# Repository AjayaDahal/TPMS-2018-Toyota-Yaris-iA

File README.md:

# TPMS monitor panel + blind-spot cameras (2018 Toyota Yaris iA)

A dash unit for the Yaris iA in two stages:

- **v1, TPMS panel (done; orderable after one fix):** receives the car's 315 MHz tyre-pressure (TPMS) sensors and shows the pressures on an OLED display, with four tyre LEDs and a rotary encoder. It is based on my ECE 6723 Embedded Systems project ([report](00-project-management/TPMS_project_report_ECE6723.pdf)).
- **v2, TPMS + blind-spot assist (designed; the carrier PCB is ready to order):** adds two mirror cameras with car/motorcycle detection on a Raspberry Pi 4, shown on your SunFounder TS-7 7" HDMI touch display (1024 × 600 IPS). When a vehicle is in a blind spot, an amber LED lights in that door sail; signalling towards it sounds a sharp beep and shows that camera. The touch screen replaces the v1 encoder, buttons and OLED, and the mute button too: the buzzer sits inside the unit and every beep stops by itself (a blind-spot beep after 4 s, while the LED keeps flashing). Both car USB passthroughs from v1 move into a printed twin wing on the unit's side, in v1's Ø25.8 × 23.8 mm double-D cuts. A 100 × 100 mm 2-layer ESP32 carrier board does the TPMS radio, the blinker inputs (wired to the lamp feeds), the speed gate (the car's own speed from your Bluetooth OBD-II dongle, GPS as the fallback), the alerts and the Pi's power sequencing. The display, the Pi and the board share one 3D-printed enclosure.

**v1 hardware:**
- **Receiver:** CC1101 module (EBYTE E07-M1101D) on 315 MHz. The report's original MX-05V superregenerative receiver can still be fitted for comparison.
- **MCU:** ESP32 DevKit V1 (DOIT, 30-pin).
- **Display:** Newhaven NHD-2.7-12864WDW3 (128×64 OLED, SSD1322, SPI).
- **Power:** 12 V ACC → protection → 5 V switcher → 3.3 V LDO.

## Interactive 3-D Viewer & Quick Start

```bash
python3 04-viewer/serve_viewer.py    # -> http://127.0.0.1:28776/viewer/
```

The viewer shows the car blueprint with both cameras, LEDs and harnesses and a live blind-spot simulator, the v2 2-layer board inside the printed enclosure, and the v1 panel. It also has the checklists (collect, buy, measure, bench tests, tools, build steps) and the v2 premortem with its order gate.

## Repository Map

| Folder | Content |
|---|---|
| [00-project-management](00-project-management/README.md) | [PREMORTEM.md](00-project-management/PREMORTEM.md) (v1), [PREMORTEM_v2.md](00-project-management/PREMORTEM_v2.md) (v2: corrections, ranked failure stories, order gate, bench tests, next steps), [TPMS_project_report_ECE6723.pdf](00-project-management/TPMS_project_report_ECE6723.pdf) |
| [01-hardware](01-hardware/README.md) | v1: KiCad 10 project (schematic, PCB, libraries, `scripts/`), [design_audit.md](01-hardware/docs/design_audit.md), `tpms_panel.step`, [1:1 car fit template](01-hardware/docs/tpms_panel_fit_template_1to1.pdf). v2: [v2/carrier/](01-hardware/v2/carrier/README.md) (the 2-layer carrier PCB: generator, KiCad project, order steps, bring-up, rework), [enclosure/](01-hardware/enclosure/README.md) (printed enclosure and mirror/door mounts: generators + STLs), [v2 fit template](01-hardware/docs/v2_fit_template_1to1.pdf), [pin-map audit](01-hardware/v2/check_pinmap.py) |
| [02-firmware](02-firmware/README.md) | [bringup/](02-firmware/bringup/README.md): ESP32 PlatformIO self-test and 315 MHz TPMS decoder. [v2/](02-firmware/v2/README.md): v2 safety logic, pin map and host unit tests |
| [03-manufacturing](03-manufacturing/README.md) | v1 JLCPCB Gerber/drill zip (`production/tpms_panel_gerbers_jlcpcb.zip`) & BOM CSV; v2 carrier (`v2_carrier/`): Gerber zip, JLCPCB BOM + CPL, hand-solder list |
| [04-viewer](04-viewer/README.md) | Offline Three.js r160 3-D viewer (`viewer/`), KiCad renders (`renders/`), `make_viewer.py`, `sync_plan.py`, `serve_viewer.py` |
| [05-Audit-Subsystems](05-Audit-Subsystems/README.md) | Audit of every subsystem with its own premortem (17 pages), the scorecard and top risks, and [run_checks.py](05-Audit-Subsystems/run_checks.py), which re-runs every automated check |

> **Sensors:** the Yaris iA's own TPMS is indirect (ABS-based, no wheel sensors). Four GM/Schrader EG53MA4 sensors were added to the tyres, and this panel is their receiver.

> **v1 status: ready to order after one fix.** The audit found the regulator's heatsink pour split by a track ([V1-01](05-Audit-Subsystems/14-v1-panel.md)): fix it in the build script and rebuild first. The outline was accepted from the in-car paper fit (board 1 mm smaller than the opening on the sides and bottom), and the USB holes are Ø25.8 mm for the measured 25.16 mm thread.
> The order file is `03-manufacturing/production/tpms_panel_gerbers_jlcpcb.zip`. If the 7" display takes the console opening (v2 Option A), v1 has no place in the car: order it only for the dash-top option or as a TPMS-only first step.

> **v2 status: the carrier PCB (rev A) is ready to order.**
> - Done: the electrical design and pin map (audited); the safety logic (166 host checks); the 2-layer carrier PCB, generated and checked (ERC/DRC 0, JLCPCB BOM + CPL under-$59 hybrid: ~$53–$57 merchandise for 5 boards with 2 assembled so Global Standard Direct Line unlocks, plus 8 hand-solder SMD parts from LCSC: [order steps](01-hardware/v2/carrier/README.md#order-it-at-jlcpcb)); the printed enclosure for the TS-7 (63 fit checks) and the mirror camera and door LED mounts (28 checks).
> - Before you order: print the 1:1 assembly drawing and set the real parts on it (G7), then check JLCPCB's quote and placement preview (G8): [order gate](00-project-management/PREMORTEM_v2.md#order-gate-for-the-v2-pcb).
> - Before you print or install: every part on hand (G3), a mock-up in the car (G5), the TS-7's and the passthroughs' measurements and a test print (G6: SunFounder publishes no drawing, see the [enclosure README](01-hardware/enclosure/README.md#measure-first-then---set)), and the blinker wire in each door (G9).

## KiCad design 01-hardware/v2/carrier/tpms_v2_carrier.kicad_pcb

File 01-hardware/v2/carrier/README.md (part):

# v2 carrier PCB, rev A

100 × 100 mm, 2 layers, 1.6 mm, 1 oz copper both sides, lead-free HASL, tented vias. It carries the ESP32 DevKit and the CC1101 module on sockets, and powers the Raspberry Pi 4, the TS-7 display and itself from the car's 12 V ACC. It also senses both blinkers and drives the door LEDs, the piezo (J4 "BUZ": the piezo sits inside the dash unit, and J4's button pins 1–2 stay free), the lid fan, the Pi link (UART, plus I2C the Pi switches on) and the GPS port. It sits behind the Pi in the [printed enclosure](../../enclosure/README.md), parts facing the lid. Its back, the side facing the Pi, carries the signature: the [AjayaDesign](https://ajayadesign.com/) logo over "Designed by Ajaya Dahal for his Basanti 2018, Toyota Yaris iA".

Everything here is generated. Don't edit the KiCad files by hand: change the Python and rebuild.

| File | What |
|---|---|
| [carrier_design.py](carrier_design.py) | The circuit: every part, net, value, LCSC number, DNP and hand-solder flag |
| [carrier_layout.py](carrier_layout.py) | Placement, enclosure keep-outs, the high-current straps, and where the signature sits |
| [build_carrier.py](build_carrier.py) | Generator: schematic → ERC → board → placement checks → straps and GND fan-out → Freerouting (plus a repair pass) → pours → DRC with schematic parity → Gerbers, BOM, CPL, PDFs |
| [make_signature_art.py](make_signature_art.py) → `signature_art.json` | The signature's artwork, as filled polygons: the mark from the website's favicon, and the words in JetBrains Mono Bold, the website's typeface (SIL Open Font License; downloaded once). It checks every stroke and gap is at least 0.18 mm, for JLCPCB's 0.153 mm silkscreen minimum. To change the words, edit them there, run it with plain Python (fontTools, shapely), then rebuild: the copper doesn't change |
| `tpms_v2_carrier_route.ses` / `.json` | The route of record and the board fingerprint it belongs to |
| [docs/](docs/) | Schematic PDF, 1:1 assembly drawing, copper plots, renders |
| [03-manufacturing/v2_carrier/](../../../03-manufacturing/v2_carrier/) | **What you upload:** Gerber zip, JLCPCB BOM and CPL, and the hand-solder and DNP list |

Rebuild (KiCad 10, Java 21+, Freerouting 2.5):

```powershell
& "$env:LOCALAPPDATA\Programs\KiCad10\bin\python.exe" build_carrier.py
```

The route of record is committed: `tpms_v2_carrier_route.ses` (the Freerouting session) and `tpms_v2_carrier_route.json` (the fingerprint of the board it belongs to: parts, pads, nets, straps, rules). A rebuild of the same board reuses it, even on a fresh clone, so changing values, text or docs never changes the copper (`--reroute` forces a new route). Freerouting isn't deterministic and often leaves a few connections behind in the crowded spots. So each attempt gets a repair pass on the routed board, and the build runs up to four attempts (`--attempts`) until one leaves nothing unconnected by KiCad's count; one attempt takes 10–25 minutes. The DRC at the end is the gate: the build exits with code 2 and "do NOT order yet" if anything is unconnected. Then check the pin map against the netlist: `python ..\check_pinmap.py`.

## The circuit in one screen

| Block | Parts | Notes |
|---|---|---|
| 12 V in (J1) | 4 A NANO2 fuse → SMCJ24CA TVS → SUD50P06-15 P-FET (−60 V, reverse battery) → π filter (6.8 µH, 3 × 10 µF, 47 µF electrolytic for damping) → 10 mΩ shunt | INA226 at 0x40 measures the 12 V input voltage and the current to both bucks and the piezo |
| 5V_PI (J5) | TPS54560B, 441 kHz, 6.8 µH, SS56C (5 A / 60 V), 4 × 47 µF → 5.17 V, 5 A | 10 mΩ shunt + INA226 at 0x41; SMBJ6.0CA clamp; EN start delay ~1.3 s; `PI_INHIBIT` (GPIO26) can only hold it off; rail-up divider to GPIO15 |
| 5V_ESP | TPS54560B, 485 kHz → 5.17 V, 1 A | SS14 into the DevKit's VIN (a USB-powered DevKit can't back-feed the board); XC6206 → 3V3 for the I2C chips; ferrite → 3V3_RF for the CC1101 |
| Inputs | 3 × ICPL-356-50C SOP-4 optos (CTR 200–400 %, 80 V): left and right blinker, AUX (J1 pin 3) | 2 × 1.2 kΩ + indicator LED per input; each lamp return has its own pin |
| Outputs | 2 × AO3400A door LEDs (PWM), 2N7002 piezo (12 V from after the shunt, through a PTC), AO3400A fan (on by default) | — |
| Monitors | TMP75 (0x48) board temperature, beside the Pi buck; TCA9534 (0x20) expander: AUX in, fan, the Pi's I2C-enable line (input), 5 spare pins | — |
| Pi link (J6) | UART: Pi UART0 ↔ ESP32 UART2 through 1 kΩ / 4.7 kΩ. I2C: the Pi's I2C6 (GPIO22/23) onto the carrier bus through two 2N7002 switches (Q901/Q902) | Only the Pi's GPIO18 turns the switches on, and it also powers their Pi-side pull-ups (R911/R912): off, halted or booting, the Pi can't touch the ESP32's bus. See [Connecting the Pi](#connecting-the-pi) |
| Ports | J2/J3 doors, J4 piezo (`BUZ`), J6 Pi link, J7 GPS (JST-GH); J8 fan | GPS is optional: a fallback speed source after the OBD-II dongle, on the standard 6-pin Pixhawk pinout |

Every ESP32 signal passes a series resistor next to its DevKit pin. It limits fault current, and it's a cut point for rework.

## Order it at JLCPCB

1. **PCB:** upload `tpms_v2_carrier_gerbers_jlcpcb.zip`. Choose:
   - layers 2, 100 × 100 mm, 1.6 mm, quantity 5. The outline's outer edge is exactly 100.0 × 100.0 mm: its centre line is inset by half the 0.1 mm line, because a size check that counts the line would read 100.1 and leave the 100 × 100 price tier. If the quote shows anything over 100 × 100, stop: the zip is an old one;
   - lead-free HASL (or ENIG if you prefer), copper weight 1 oz on both sides;
   - via covering: "Tented" (default on 2 layers; all vias are ≥ 0.60 / 0.30 mm, so zero small-hole or POFV fee; each TPS54560B PowerPAD has 4 tented thermal vias leaving the center paste area open);
   - everything else at JLCPCB's defaults: green mask, white silk, no gold fingers, castellated holes or impedance control. An option that adds a fee means something was mis-detected: this board needs none. The silkscreen prints on both sides at no extra cost; the back's is the signature.

   The order number prints where the silkscreen says `JLCJLCJLCJLC` (top left), so choose "Specify a location".
2. **Assembly:** PCB Assembly on:
   - **Economic**, top side only, quantity **2**;
   - upload `tpms_v2_carrier_bom_jlcpcb.csv` and `tpms_v2_carrier_cpl_jlcpcb.csv`.

   Every line (**51 BOM lines** and **169 placements**: 41 basic + 4 preferred + 6 extended) should match its LCSC part, with **no line marked unmatched or "not placed"**. The 8 hand-soldered SMD parts (7 power parts plus the TMP75), the 5 THT connectors, and the DNP rework options are in `tpms_v2_carrier_hand_solder_and_dnp.csv`.
3. **Placement preview:** check every polarized part before you confirm:
   - the diodes: SS56C at D201/D301, SS14 at D304, the 1N4148Ws; the SMCJ24CA at D101 and SMBJ6.0CA at D203/D302 are bidirectional, so either way is fine;
   - the LEDs: D102, D204, D303, D305, D501, D503, D505. JLCPCB marks the cathode `−` and the anode `+`; the `−` must sit on the silkscreen's cathode side (the yellow D303/D501/D503 were 180° off before [PCB-30](../../../05-Audit-Subsystems/11-carrier-pcb.md));
   - pin 1 of every IC: U101, U201, U202, U301, U302, U501–U503, U802 (U801 is hand-soldered);
   - the three inductors L101, L201, L301 are unpolarized.

   The CPL rotations are fitted to JLCPCB's own footprints by the build, and it reports the worst fit (0.30 mm), but the preview is the last check.
4. **Price & shipping threshold (why the hybrid split exists):** JLCPCB's **Global Standard Direct Line** shipping (cheap, ~$5–$10) requires the **merchandise total to stay under $59.00**. Putting all 177 SMD parts on PCBA pushed the merchandise total to **$76.10**, which disabled Global Standard Direct Line and forced **UPS Express Saver (DDP)** ($59.99 shipping + $26.64 duties + $4.44 disbursement = **$167.17 total**). Moving 8 large or easy SMD parts (7 two/three-pad power parts and the SOIC-8 TMP75) to hand-solder keeps JLCPCB merchandise at **~$53–$57 (< $59.00)**, keeping all 169 fine-pitch, PowerPAD, inductor and 0603 parts on machine assembly while unlocking Global Standard Direct Line and saving **~$80–$90** overall: see [Cost](#cost). **The quote is the real number: if it reads ≥ $59.00, stop and don't pay the UPS price.**

## Hand soldering

JLCPCB machine-reflows all 169 hard/tiny SMD parts (both PowerPAD bucks, all three 10×10 mm inductors, both 0.5 mm INA226s, TCA9534, all 5 JST-GH sockets, all 93 0603s, LEDs, diodes, and SOT-23s). After the boards arrive, you hand-solder **8 SMD parts** (7 chunky 2/3-pad power parts and one 1.27 mm-pitch SOIC-8, ~10 min with a regular chisel-tip iron) and **5 through-hole connectors** (full list with LCSC numbers in `tpms_v2_carrier_hand_solder_and_dnp.csv`).

**Why the inductors stay on PCBA and the TMP75 moved to hand-solder (pre-order audit, [PCB-28](../../../05-Audit-Subsystems/11-carrier-pcb.md)):** the footprint was drawn for Sunlord `MWSA1004S-6R8MT` (LCSC `C408485`), and that part is *JLCPCB-assembly stock only*: LCSC doesn't sell it loose, and the "equivalents" on other sites were never checked against this footprint, saturation current or DCR. A wrong inductor there would kill both bucks. So JLCPCB places the exact part, and the TMP75 (which costs about the same fee) comes off instead: it is a plain SOIC-8, stocked at LCSC, and the board works fully without it (the firmware doesn't read it yet; it is only a temperature monitor).

Order the 8 SMD parts from **LCSC** — every one is the exact part the footprint was made for and was in stock at the audit (2026-11-27); about $5–$6 of parts for 2 boards plus LCSC shipping. Don't substitute. Fit them first while the board lies flat: smallest first (`F601`, `F901`, `R104`, `R211`, `F101`), then `U801`, `Q101` and `C104`, then the 5 THT connectors. The board won't power up without `F101`, `Q101`, `R104` (12 V in) and `R211` (Pi 5 V).

| Ref | Part | Buy (qty for 2 boards) |
|---|---|---|
| A1 | 2 × 1×15 female headers, 2.54 mm, standard 8.5 mm tall | Lab inventory. Footprint has both DevKit widths (`0.9` / `1.0`). **Measure your DevKit first** and solder the matching row |
| A2 | 2×4 female header, 2.54 mm (or two 1×4 strips side by side) | Lab inventory. SMA end toward top edge (`CC1101: SMA END`) |
| J1 | 4-pole screw terminal, 5.08 mm: or 2 blue 2-pole blocks, slid together | Lab inventory. Wire entries toward board edge |
| J5 | 6-pole screw terminal, 5.08 mm: or 3 blue 2-pole blocks | Lab inventory. Wire entries toward board edge |
| J8 | 1×2 right-angle pin header, 2.54 mm | Lab inventory. Lid fan |
| C104 | 47 µF / 50 V electrolytic, 6.3×7.7 SMD | LCSC `C970679` (`RVT1H470M0607`), qty 2 (LCSC minimum may be 20 — still under $2), `+` toward `12V_PROT`. Its `−` pad has GND thermal spokes |
| F101 | 4 A 2410 NANO2 fast SMD fuse | LCSC `C27515` (Littelfuse `0451004.MRL`), qty 2 |
| F601, F901 | 0.5 A / 60 V 1812 PTC polyfuse | LCSC `C70113` (`mSMD050-60V`), qty 4 |
| Q101 | −60 V P-MOSFET TO-252 DPAK, ≤ 25 mΩ | LCSC `C7503186` (`SUD50P06-15`), qty 2. Never a high-Rds(on) part like `FQD11P06` |
| R104, R211 | 10 mΩ 1 % 2 W 2512 current shunt | LCSC `C192580` (Viking `RLM25FEER010`), qty 4 |
| U801 | TMP75AIDR temperature sensor, SOIC-8 | LCSC `C30389`, qty 2. Pin 1 dot to the silkscreen dot. Optional: leave it off and the board still runs |

Add 1–2 spares of each small part; a dropped 1812 or 2512 is common. All through-hole ground pins, `C104`'s `−` pad and `U801`'s GND pins connect to the L1/L2 GND pours through thermal reliefs, and the other power parts sit on small local pours, so everything solders cleanly on this 2-layer HASL board with a standard 60–80 W chisel tip and flux. The Economic PCBA stencil also pastes the hand-solder pads, so they arrive tinned.

## Connectors from your lab

Every connector on the board mates with something in the lab inventory; nothing needs a JST-GH crimper.

| On the board | Footprint | From your lab | Notes |
|---|---|---|---|
| J1 (12 V in) | 4-pole 5.08 mm screw terminal, 1.3 mm holes | 2 blue 2-pole screw blocks, slid together | 5.0 or 5.08 mm pitch both fit (0.3 mm play a hole). Wire entries toward the board edge |
| J5 (5 V out) | 6-pole, the same | 3 blue 2-pole blocks | So 5 blocks a board, 10 for two |
| J2, J3, J4 (doors, piezo) | JST-GH 4-pin, assembled by JLCPCB | 3 × 4-pin elechawk GH1.25 → Dupont pigtails (20 cm, pre-crimped) | The door cable joins the pigtail with solder and heat-shrink: a Dupont joint doesn't lock and the door run vibrates |
| J6 (Pi link) | JST-GH 6-pin | 1 × 6-pin pigtail + your 40-pin GPIO ribbon | See [Connecting the Pi](#connecting-the-pi) |
| J7 (GPS) | JST-GH 6-pin, Pixhawk pinout | The GPS's own GH cable if it has one, or a 6-pin pigtail | Pins: 1 5 V, 2 TX (to the GPS's RX), 3 RX (from its TX), 4 SCL, 5 SDA, 6 GND. Check the GPS cable against this first; R907/R908 swap TX and RX |
| J8 (fan) | 1×2 2.54 mm right-angle male header | A right-angle strip from the Dupont kit, or a straight one bent 90° | The fan's Dupont plug fits it |
| A1 (DevKit) | 2 × 1×15 female 2.54 mm | Female header strips | Standard 8.5 mm tall: the enclosure allows 16 mm over the board for socket plus DevKit. Cutting a strip costs one position a cut, so plan ~1.5 × 1×40 strips a board |
| A2 (CC1101) | 2×4 female 2.54 mm | A 2×4 socket or two 1×4 strips side by side | — |
| J9–J14 (DNP) | 2.54 mm headers | Male strips, only if you ever need them (`J9` I2C + expander, `J10` alt CC1101, `J11` ext 12 V, `J12` ext 5 V ESP, `J13` `SAFE PWR`, `J14` `SAFE PI`) | — |

The Preciva PR-3254 crimps Dupont (and JST-XH) contacts, not the 1.25 mm GH ones; the pre-crimped pigtails cover all of those. The JST-XH kit isn't used on this board. **Count before you order:** 3 × 4-pin and 1–2 × 6-pin GH pigtails a unit, 5 two-pole blocks a board, and the female strips. The pigtails' Dupont ends are usually female: check yours, it decides how the Pi's ribbon joins J6.

## Connecting the Pi

J6 (GH-6, silkscreen `PI`) is the whole Pi ↔ ESP32 link. At the Pi it uses your 40-pin GPIO ribbon cable: its IDC plug stands ~12.5 mm on the header, where straight Dupont plugs (~22 mm) would hit this board.

| J6 pin | Signal | Pi header pin | Pi GPIO | On the carrier |
|---|---|---|---|---|
| 1 | GND | 6 | — | GND |
| 2 | Pi TX | 8 | GPIO14, UART0 TXD | R901 1 kΩ → ESP32 IO16 (UART2 RX); test pad TP15 |
| 3 | Pi RX | 10 | GPIO15, UART0 RXD | R902 4.7 kΩ ← ESP32 IO17 (UART2 TX); test pad TP16 |
| 4 | I2C enable | 12 | GPIO18 | Gates of Q901/Q902, the Pi-side pull-ups R911/R912, and expander P2 through R903 (the ESP32 reads it) |
| 5 | SDA | 15 | GPIO22, I2C6 SDA | Q901 → I2C_SDA |
| 6 | SCL | 16 | GPIO23, I2C6 SCL | Q902 → I2C_SCL |

**Wiring it:**

1. Push the ribbon's IDC onto the Pi's GPIO header with the red stripe (conductor 1) on pin 1, the header's end away from the USB ports. Conductor n is then pin n.
2. Cut the ribbon ~10 cm from that plug and peel off conductors 6, 8, 10, 12, 15 and 16. Trim the other 34 back a few millimetres and seal their cut edge with heat-shrink or tape: pins 2 and 4 are the Pi's 5 V. Strip 3 mm of each of the six.
3. Join each to its pigtail lead from the table. For the car, solder and heat-shrink them. For the bench, crimp male Dupont pins on the ribbon wires (PR-3254; the 28 AWG ribbon wire is below its 26 AWG die, so fold the stripped end double) and plug them into the pigtail's female housings.
4. Before power, and before the IDC goes on the Pi, plug the pigtail into J6 and ring each join from its IDC hole (a male Dupont pin in the hole makes a probe point) to the board: GND, TP15, TP16, R903, Q901, Q902. Check that the 5 V holes (2, 4) reach nothing.

**Pi set-up**, in `config.txt`, with no `console=serial0,...` in `cmdline.txt`:

```
enable_uart=1
dtoverlay=disable-bt     # the PL011 UART on GPIO14/15 carries the ESP32 link
dtoverlay=i2c6           # I2C6 on GPIO22/23 (pins 15/16): /dev/i2c-6
gpio=18=op,dl            # GPIO18 low from power-on: the Pi stays off the carrier's I2C bus
```

**The I2C bus has one master at a time.** The ESP32 owns it: it polls the INA226s, the TMP75 and the expander all the time, and the Pi's I2C controller can't arbitrate with a second master. So the Pi raises GPIO18 only when the ESP32 isn't using the bus:

- **On the bench, or to rescue a dead ESP32:** DevKit out of its socket (or its EN button held down), then on the Pi `pinctrl set 18 op dh` and `i2cdetect -y 6` lists 0x20, 0x40, 0x41 and 0x48 (and the GPS compass if R909/R910 are fitted). `pinctrl set 18 op dl` when you're done.
- **With the ESP32 running:** only after a hand-over on the UART (a `$I2C` request and grant, reserved in the [protocol](../../../02-firmware/v2/README.md), not written yet). Until then the Pi gets the readings from the ESP32's status lines.

Why I2C6 and not the usual I2C1 (pins 3/5): I2C1 has fixed 1.8 kΩ pull-ups, and GPIO3 low wakes a halted Pi 4. A FET switch lets the carrier's lows through its body diode even when it's off, so the ESP32's polling after shutdown would have booted the Pi again ([LNK-09](../../../05-Audit-Subsystems/07-esp32-pi-link.md)).

**Other links between the two, now and later:**

- **USB:** with the lid off, a 90° micro-USB lead from the DevKit to a free Pi USB port lets the Pi flash the ESP32 (`esptool`, with automatic reset), read its log and reset it. The Wi-Fi OTA service mode is the other way in.
- **SPI isn't possible.** Every usable GPIO of the 30-pin DevKit is taken (GPIO12 must stay open), so there are no pins for an SPI slave. Its SPI bus belongs to the CC1101, and a bus can't have two masters.
- **Room to grow:** I2C devices on J9 (DNP 2×5: 3V3, GND, I2C, the expander's P3–P7 and its interrupt) are reachable from both the ESP32 and the Pi. The rest of the Pi's header (I2C1, SPI0, UART2–5) stays free on the ribbon for Pi-only add-ons.

## First power-up (bench, before the car)

Use a bench supply with a current limit, the DevKit and the CC1101 out of their sockets, and nothing on J5.

1. Look over the INA226s (U101, U202, 0.5 mm pitch) and the TCA9534 (U802) for bridges. With the power off, measure J1 + to − (more than 10 kΩ), TP4 (5V_PI) to GND and TP6 (3V3) to GND (both more than 100 Ω).
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
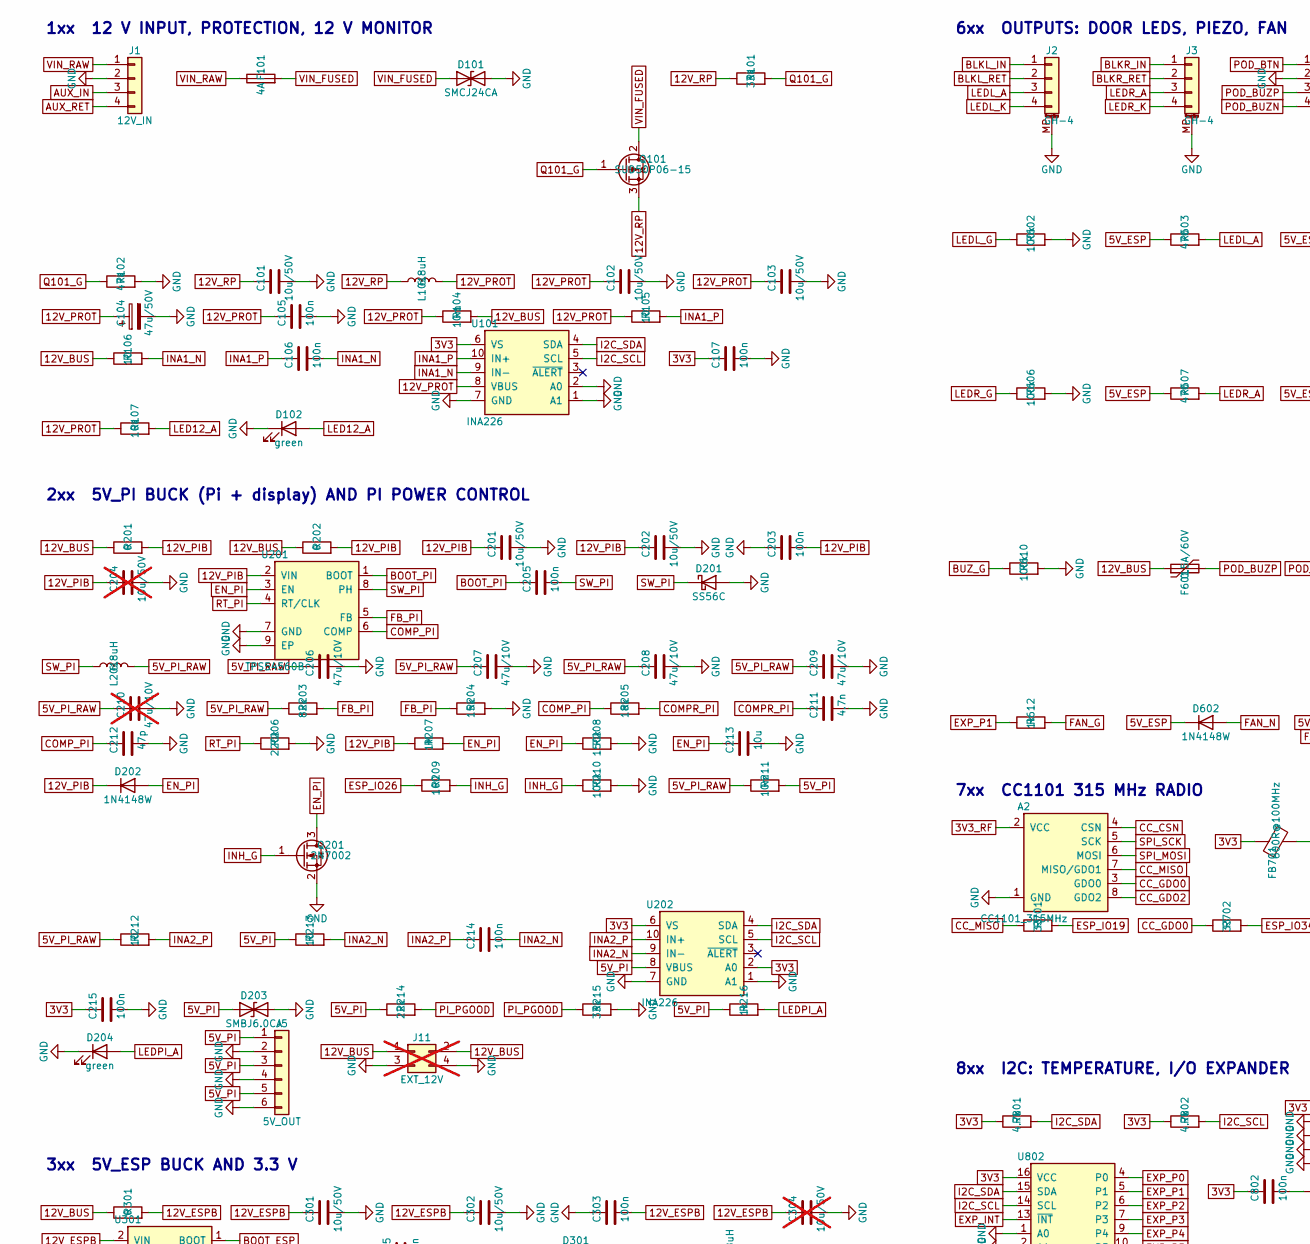
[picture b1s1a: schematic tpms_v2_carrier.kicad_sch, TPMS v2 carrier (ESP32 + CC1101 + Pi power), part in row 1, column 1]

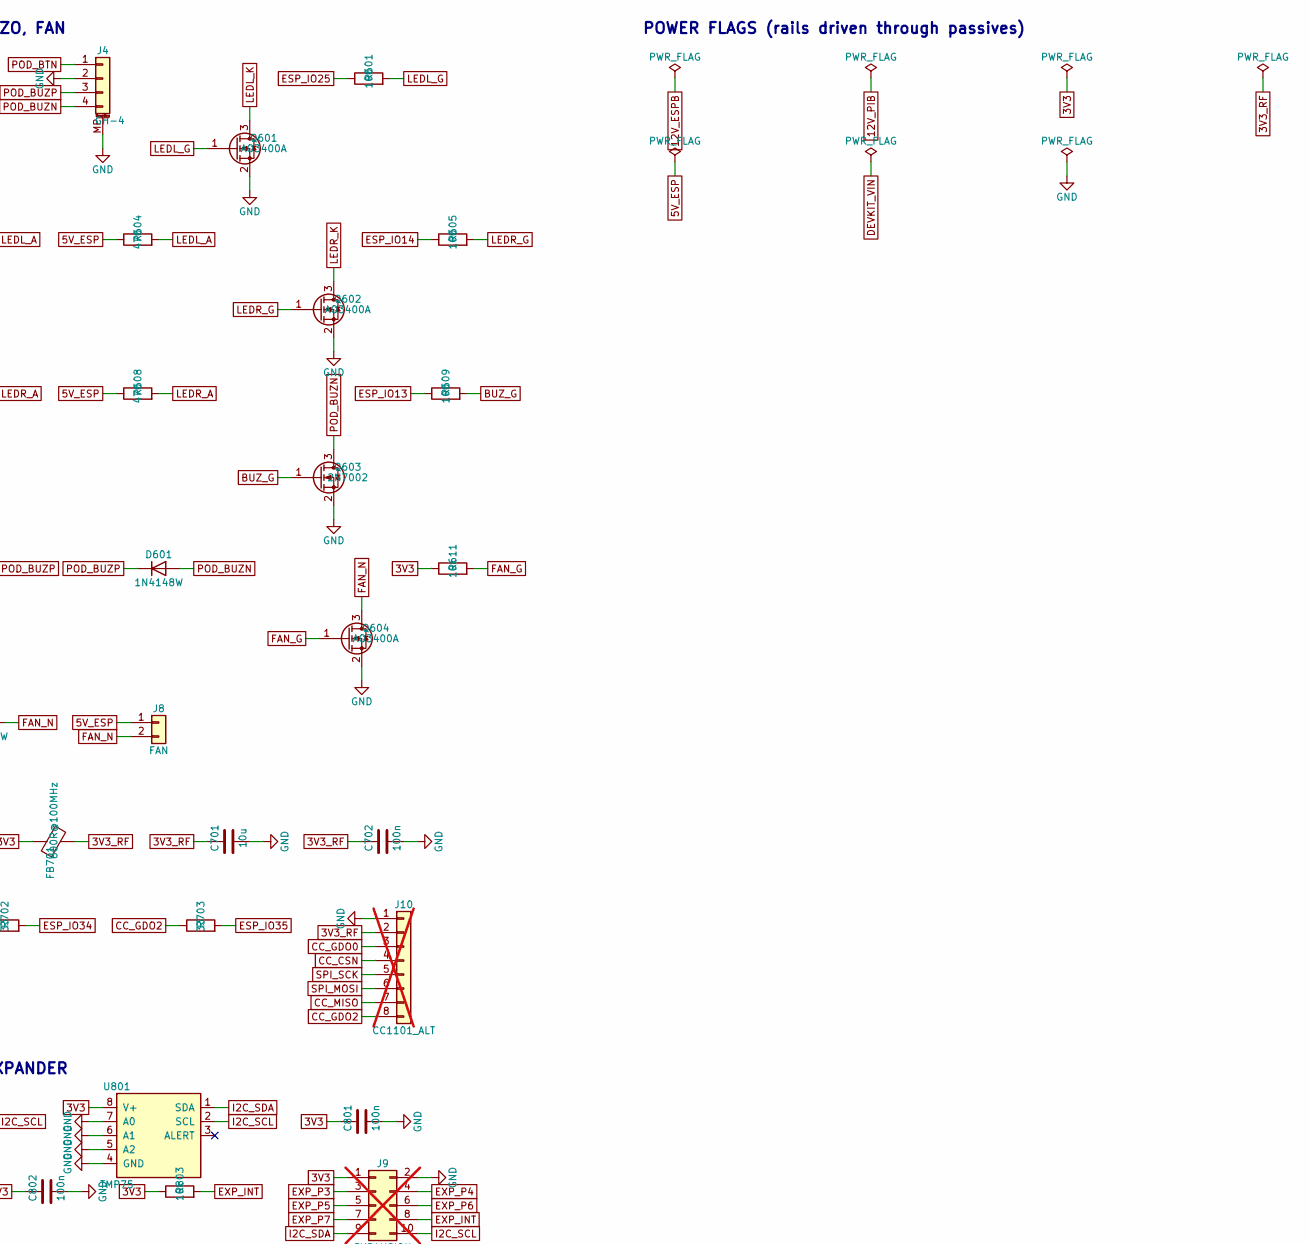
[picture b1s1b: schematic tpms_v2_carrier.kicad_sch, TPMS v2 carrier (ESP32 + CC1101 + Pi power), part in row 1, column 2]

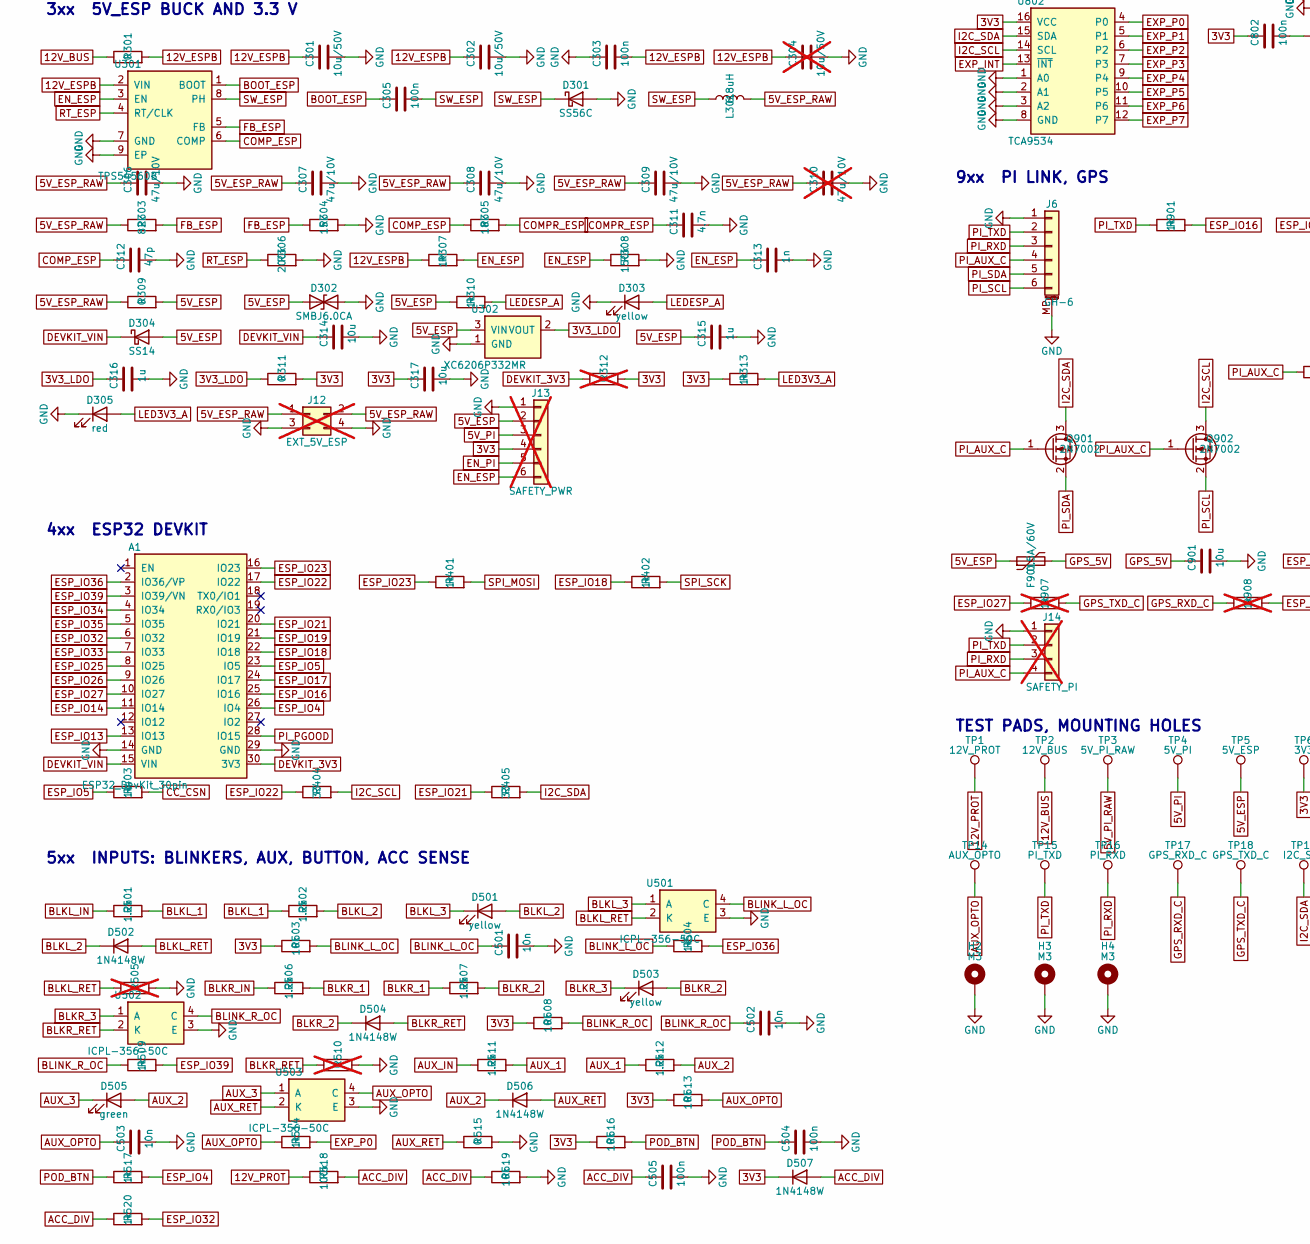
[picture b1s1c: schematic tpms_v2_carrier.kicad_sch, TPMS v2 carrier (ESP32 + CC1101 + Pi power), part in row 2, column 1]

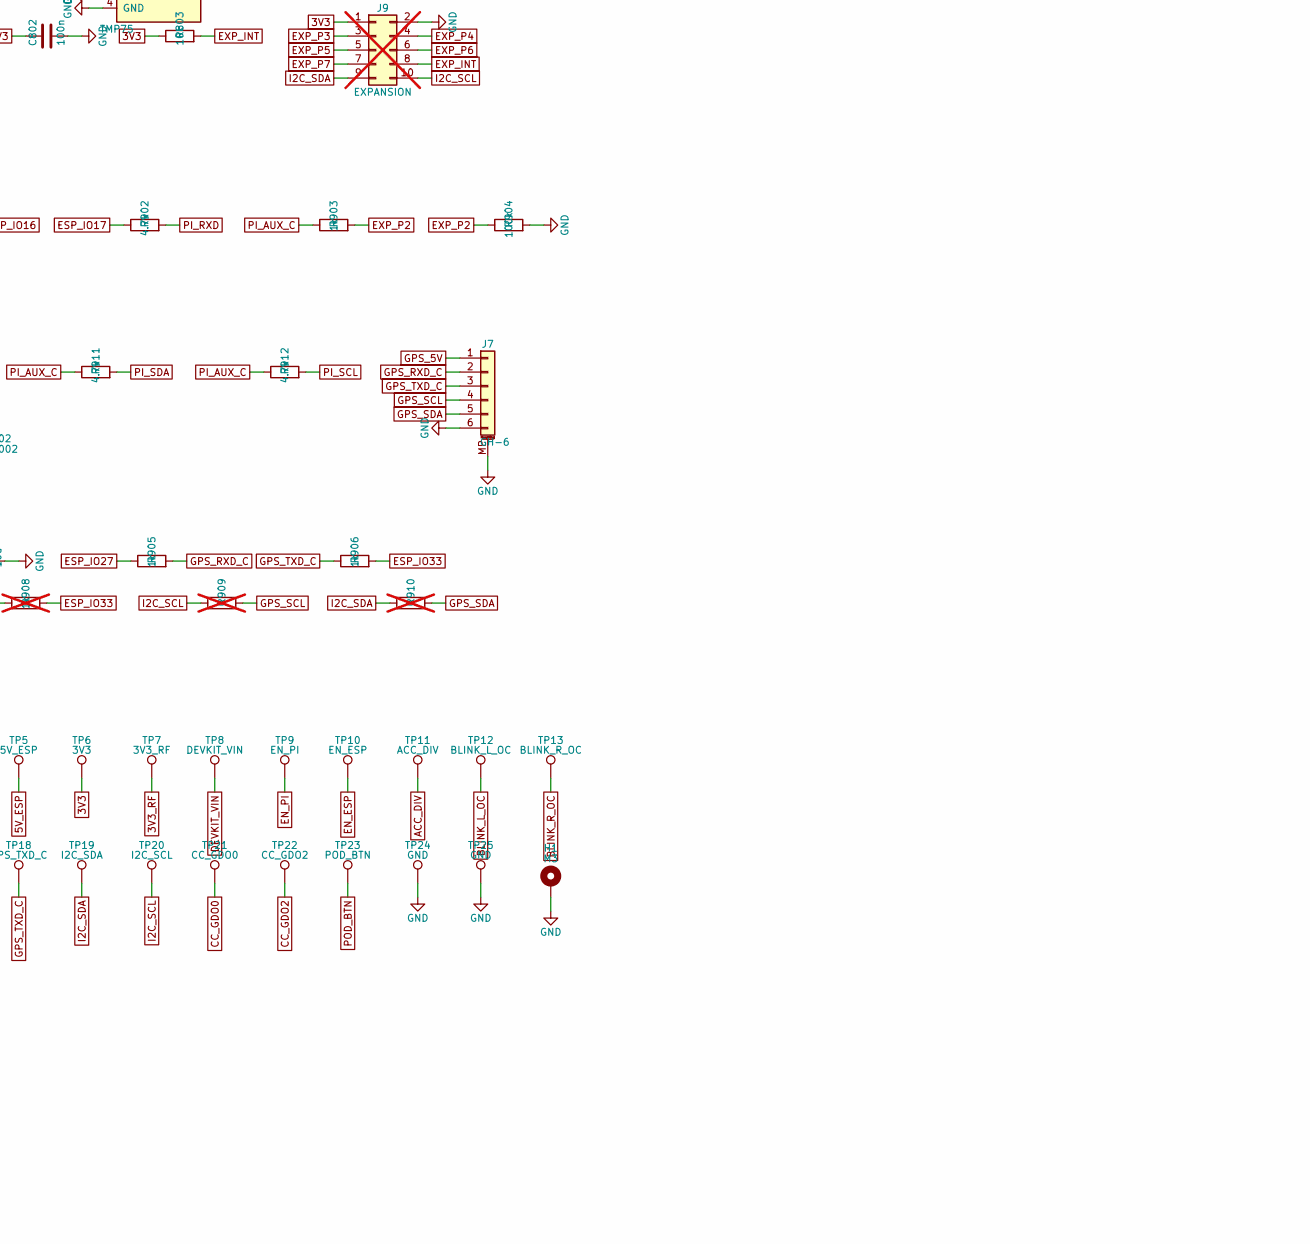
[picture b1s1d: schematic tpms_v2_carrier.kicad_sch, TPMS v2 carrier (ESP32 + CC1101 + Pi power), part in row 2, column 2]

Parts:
A1: ESP32_DevKit_30pin; ESP32_DevKit_30pin_Sockets; MPN 2x 1x15 2.54 mm female header, 8.5 mm (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
A2: CC1101_315MHz; CC1101_2x4_Socket; MPN 2x4 2.54 mm female header, 8.5 mm (CC11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
C101, C102, C103, C201, C202, C301, C302: 10u/50V; C_1206_3216Metric; LCSC C13585
C104: 47u/50V; CP_Elec_6.3x7.7; MPN 47u/50V electrolytic, 6.3x7.7 SMD (LCSC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
C105, C106, C107, C203, C205, C214, C215, C303, C305, C504, C505, C702, C801, C802: 100n; C_0603_1608Metric; LCSC C14663
C204, C304: 10u/50V; C_1206_3216Metric; LCSC C13585; not fitted
C206, C207, C208, C209, C306, C307, C308, C309: 47u/10V; C_1206_3216Metric; LCSC C96123
C210, C310: 47u/10V; C_1206_3216Metric; LCSC C96123; not fitted
C211, C311: 4.7n; C_0603_1608Metric; LCSC C53987
C212, C312: 47p; C_0603_1608Metric; LCSC C1671
C213, C314, C901: 10u; C_0805_2012Metric; LCSC C15850
C313: 1n; C_0603_1608Metric; LCSC C1588
C315, C316: 1u; C_0603_1608Metric; LCSC C15849
C317, C701: 10u; C_0603_1608Metric; LCSC C96446
C501, C502, C503: 10n; C_0603_1608Metric; LCSC C57112
D101: SMCJ24CA; D_SMC; MPN SMCJ24CA; LCSC C41411747
D102, D204, D505: green; LED_0805_2012Metric; LCSC C2297
D201, D301: SS56C; D_SMC; MPN SS56C; LCSC C18199187
D202, D502, D504, D506, D507, D601, D602: 1N4148W; D_SOD-123; MPN 1N4148W; LCSC C81598
D203, D302: SMBJ6.0CA; D_SMB; MPN SMBJ6.0CA; LCSC C2925451
D303, D501, D503: yellow; LED_0805_2012Metric; LCSC C2296
D304: SS14; D_SMA; MPN SS14; LCSC C2480
D305: red; LED_0603_1608Metric; LCSC C2286
F101: 4A; Fuse_Littelfuse-NANO2-451_453; MPN 4A 2410 NANO2 fast SMD fuse (LCSC C2751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
F601, F901: 0.5A/60V; Fuse_1812_4532Metric; MPN 0.5A/60V 1812 PTC polyfuse (LCSC C70113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
FB701: 600R@100MHz; L_0603_1608Metric; MPN Sunlord GZ1608D601TF; LCSC C1002
H1, H2, H3, H4: M3; MountingHole_3.2mm_M3_Pad_Via
J1: 12V_IN; TerminalBlock_Phoenix_MKDS-1,5-4-5.08_1x04_P5.08mm_Horizont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; MPN 4-pos 5.08 mm screw terminal, horizonta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
J2, J3, J4: GH-4; JST_GH_SM04B-GHS-TB_1x04-1MP_P1.25mm_Horizontal; MPN JST SM04B-GHS-TB(LF)(SN); LCSC C189895
J5: 5V_OUT; TerminalBlock_Phoenix_MKDS-1,5-6-5.08_1x06_P5.08mm_Horizont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; MPN 6-pos 5.08 mm screw terminal, horizonta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
J6, J7: GH-6; JST_GH_SM06B-GHS-TB_1x06-1MP_P1.25mm_Horizontal; MPN JST SM06B-GHS-TB(LF)(SN); LCSC C133065
J8: FAN; PinHeader_1x02_P2.54mm_Horizontal; MPN 1x2 2.54 mm right-angle male header (fa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
J9: EXPANSION; PinHeader_2x05_P2.54mm_Vertical; not fitted
J10: CC1101_ALT; PinHeader_1x08_P2.54mm_Vertical; not fitted
J11: EXT_12V; PinHeader_2x02_P2.54mm_Vertical; not fitted
J12: EXT_5V_ESP; PinHeader_2x02_P2.54mm_Vertical; not fitted
J13: SAFETY_PWR; PinHeader_1x06_P2.54mm_Vertical; not fitted
J14: SAFETY_PI; PinHeader_1x04_P2.54mm_Vertical; not fitted
L101, L201, L301: 6.8uH; L_Sunlord_MWSA1004S; MPN Sunlord MWSA1004S-6R8MT; LCSC C408485
Q101: SUD50P06-15; TO-252-2; MPN -60V P-MOSFET TO-252 DPAK, <=25 mOhm, G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
Q201, Q603, Q901, Q902: 2N7002; SOT-23; MPN 2N7002; LCSC C8545
Q601, Q602, Q604: AO3400A; SOT-23; MPN AOS AO3400A; LCSC C20917
R101, R215: 33k; R_0603_1608Metric; LCSC C4216
R102: 47k; R_0603_1608Metric; LCSC C25819
R104, R211: 10m; R_2512_6332Metric; MPN 10 mOhm 1% 2W 2512 current shunt (LCSC 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
R105, R106, R212, R213: 10; R_0603_1608Metric; LCSC C22859
R107: 10k; R_0805_2012Metric; LCSC C17414
R201, R202, R301, R309: 0; R_1206_3216Metric; LCSC C17888
R203, R303: 82k; R_0603_1608Metric; LCSC C23254
R204, R304: 15k; R_0603_1608Metric; LCSC C22809
R205, R305: 18k; R_0603_1608Metric; LCSC C25810
R206: 220k; R_0603_1608Metric; LCSC C22961
R207, R307: 1M; R_0603_1608Metric; LCSC C22935
R208, R308: 150k; R_0603_1608Metric; LCSC C22807
R209, R601, R605, R609: 100; R_0603_1608Metric; LCSC C22775
R210, R518, R602, R606, R610, R904: 100k; R_0603_1608Metric; LCSC C25803
R214: 22k; R_0603_1608Metric; LCSC C31850
R216, R310, R313, R401, R402, R403, R504, R509, R514, R517, R520, R612, R901, R903, R905, R906: 1k; R_0603_1608Metric; LCSC C21190
R306: 200k; R_0603_1608Metric; LCSC C25811
R311, R515: 0; R_0603_1608Metric; LCSC C21189
R312, R505, R510, R909, R910: 0; R_0603_1608Metric; LCSC C21189; not fitted
R404, R405, R701, R702, R703: 33; R_0603_1608Metric; LCSC C23140
R501, R502, R506, R507, R511, R512: 1.2k; R_0805_2012Metric; LCSC C17379
R503, R508, R513, R516, R519, R611, R803: 10k; R_0603_1608Metric; LCSC C25804
R603, R604, R607, R608: 470; R_0805_2012Metric; LCSC C17710
R801, R802, R902, R911, R912: 4.7k; R_0603_1608Metric; LCSC C23162
R907, R908: 1k; R_0603_1608Metric; LCSC C21190; not fitted
TP1: 12V_PROT; TestPoint_Pad_D1.5mm
TP2: 12V_BUS; TestPoint_Pad_D1.5mm
TP3: 5V_PI_RAW; TestPoint_Pad_D1.5mm
TP4: 5V_PI; TestPoint_Pad_D1.5mm
TP5: 5V_ESP; TestPoint_Pad_D1.5mm
TP6: 3V3; TestPoint_Pad_D1.5mm
TP7: 3V3_RF; TestPoint_Pad_D1.0mm
TP8: DEVKIT_VIN; TestPoint_Pad_D1.0mm
TP9: EN_PI; TestPoint_Pad_D1.0mm
TP10: EN_ESP; TestPoint_Pad_D1.0mm
TP11: ACC_DIV; TestPoint_Pad_D1.0mm
TP12: BLINK_L_OC; TestPoint_Pad_D1.0mm
TP13: BLINK_R_OC; TestPoint_Pad_D1.0mm
TP14: AUX_OPTO; TestPoint_Pad_D1.0mm
TP15: PI_TXD; TestPoint_Pad_D1.0mm
TP16: PI_RXD; TestPoint_Pad_D1.0mm
TP17: GPS_RXD_C; TestPoint_Pad_D1.0mm
TP18: GPS_TXD_C; TestPoint_Pad_D1.0mm
TP19: I2C_SDA; TestPoint_Pad_D1.0mm
TP20: I2C_SCL; TestPoint_Pad_D1.0mm
TP21: CC_GDO0; TestPoint_Pad_D1.0mm
TP22: CC_GDO2; TestPoint_Pad_D1.0mm
TP23: POD_BTN; TestPoint_Pad_D1.0mm
TP24, TP25: GND; TestPoint_THTPad_D2.0mm_Drill1.0mm
U101, U202: INA226; TSSOP-10_3x3mm_P0.5mm; MPN TI INA226AIDGSR; LCSC C49851
U201, U301: TPS54560B; TI_SO-PowerPAD-8; MPN TI TPS54560BDDAR; LCSC C1850354
U302: XC6206P332MR; SOT-23; MPN Torex XC6206P332MR-G; LCSC C5446
U501, U502, U503: ICPL-356-50C; SOP-4_LTV-357T_P2.54mm_Rows6.5mm; MPN ICPL-356-50CEAXW; LCSC C42432283
U801: TMP75; SOIC-8_3.9x4.9mm_P1.27mm; MPN TMP75AIDR temperature sensor, SOIC-8 (L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
U802: TCA9534; TSSOP-16_4.4x5mm_P0.65mm; MPN TI TCA9534PWR; LCSC C783615

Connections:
3V3: C107.1, C215.1, C317.1, C801.1, C802.1, D507.1 (K), FB701.1, J9.1, J13.4, R311.2, R312.2, R313.1, R503.1, R508.1, R513.1, R516.1, R611.1, R801.1, R802.1, R803.1, TP6.1, U101.6 (VS), U202.2 (A0), U202.6 (VS), U801.8 (V+), U802.16 (VCC)
3V3_LDO: C316.1, R311.1, U302.2 (VOUT)
3V3_RF: A2.2 (VCC), C701.1, C702.1, FB701.2, J10.2, TP7.1
5V_ESP: C315.1, D302.1 (A1), D304.2 (A), D602.1 (K), F901.1, J8.1, J13.2, R309.2, R310.1, R603.1, R604.1, R607.1, R608.1, TP5.1, U302.3 (VIN)
5V_ESP_RAW: C306.1, C307.1, C308.1, C309.1, C310.1, J12.1, J12.2, L301.2, R303.1, R309.1
5V_PI: D203.1 (A1), J5.1, J5.3, J5.5, J13.3, R211.2, R213.1, R214.1, R216.1, TP4.1, U202.8 (VBUS)
5V_PI_RAW: C206.1, C207.1, C208.1, C209.1, C210.1, L201.2, R203.1, R211.1, R212.1, TP3.1
12V_BUS: F601.1, J11.1, J11.2, R104.2, R106.1, R201.1, R202.1, R301.1, TP2.1
12V_ESPB: C301.1, C302.1, C303.2, C304.1, R301.2, R307.1, U301.2 (VIN)
12V_PIB: C201.1, C202.1, C203.2, C204.1, D202.1 (K), R201.2, R202.2, R207.1, U201.2 (VIN)
12V_PROT: C102.1, C103.1, C104.1, C105.1, L101.2, R104.1, R105.1, R107.1, R518.1, TP1.1, U101.8 (VBUS)
12V_RP: C101.1, L101.1, Q101.3 (S), R101.1
ACC_DIV: C505.1, D507.2 (A), R518.2, R519.1, R520.1, TP11.1
AUX_1: R511.2, R512.1
AUX_2: D505.2 (A), D506.1 (K), R512.2
AUX_3: D505.1 (K), U503.1 (A)
AUX_IN: J1.3, R511.1
AUX_OPTO: C503.1, R513.2, R514.1, TP14.1, U503.4 (C)
AUX_RET: D506.2 (A), J1.4, R515.1, U503.2 (K)
BLINK_L_OC: C501.1, R503.2, R504.1, TP12.1, U501.4 (C)
BLINK_R_OC: C502.1, R508.2, R509.1, TP13.1, U502.4 (C)
BLKL_1: R501.2, R502.1
BLKL_2: D501.2 (A), D502.1 (K), R502.2
BLKL_3: D501.1 (K), U501.1 (A)
BLKL_IN: J2.1, R501.1
BLKL_RET: D502.2 (A), J2.2, R505.1, U501.2 (K)
BLKR_1: R506.2, R507.1
BLKR_2: D503.2 (A), D504.1 (K), R507.2
BLKR_3: D503.1 (K), U502.1 (A)
BLKR_IN: J3.1, R506.1
BLKR_RET: D504.2 (A), J3.2, R510.1, U502.2 (K)
BOOT_ESP: C305.1, U301.1 (BOOT)
BOOT_PI: C205.1, U201.1 (BOOT)
BUZ_G: Q603.1 (G), R609.2, R610.1
CC_CSN: A2.4 (CSN), J10.4, R403.2
CC_GDO0: A2.3 (GDO0), J10.3, R702.1, TP21.1
CC_GDO2: A2.8 (GDO2), J10.8, R703.1, TP22.1
CC_MISO: A2.7 (MISO/GDO1), J10.7, R701.1
COMPR_ESP: C311.1, R305.2
COMPR_PI: C211.1, R205.2
COMP_ESP: C312.1, R305.1, U301.6 (COMP)
COMP_PI: C212.1, R205.1, U201.6 (COMP)
DEVKIT_3V3: A1.30 (3V3), R312.1
DEVKIT_VIN: A1.15 (VIN), C314.1, D304.1 (K), TP8.1
EN_ESP: C313.1, J13.6, R307.2, R308.1, TP10.1, U301.3 (EN)
EN_PI: C213.1, D202.2 (A), J13.5, Q201.3 (D), R207.2, R208.1, TP9.1, U201.3 (EN)
ESP_IO4: A1.26 (IO4), R517.2
ESP_IO5: A1.23 (IO5), R403.1
ESP_IO13: A1.13 (IO13), R609.1
ESP_IO14: A1.11 (IO14), R605.1
ESP_IO16: A1.25 (IO16), R901.2
ESP_IO17: A1.24 (IO17), R902.1
ESP_IO18: A1.22 (IO18), R402.1
ESP_IO19: A1.21 (IO19), R701.2
ESP_IO21: A1.20 (IO21), R405.1
ESP_IO22: A1.17 (IO22), R404.1
ESP_IO23: A1.16 (IO23), R401.1
ESP_IO25: A1.8 (IO25), R601.1
ESP_IO26: A1.9 (IO26), R209.1
ESP_IO27: A1.10 (IO27), R905.1, R907.1
ESP_IO32: A1.6 (IO32), R520.2
ESP_IO33: A1.7 (IO33), R906.2, R908.2
ESP_IO34: A1.4 (IO34), R702.2
ESP_IO35: A1.5 (IO35), R703.2
ESP_IO36: A1.2 (IO36/VP), R504.2
ESP_IO39: A1.3 (IO39/VN), R509.2
EXP_INT: J9.8, R803.2, U802.13 (~INT)
EXP_P0: R514.2, U802.4 (P0)
EXP_P1: R612.1, U802.5 (P1)
EXP_P2: R903.2, R904.1, U802.6 (P2)
EXP_P3: J9.3, U802.7 (P3)
EXP_P4: J9.4, U802.9 (P4)
EXP_P5: J9.5, U802.10 (P5)
EXP_P6: J9.6, U802.11 (P6)
EXP_P7: J9.7, U802.12 (P7)
FAN_G: Q604.1 (G), R611.2, R612.2
FAN_N: D602.2 (A), J8.2, Q604.3 (D)
FB_ESP: R303.2, R304.1, U301.5 (FB)
FB_PI: R203.2, R204.1, U201.5 (FB)
GND: A1.14 (GND), A1.29 (GND), A2.1 (GND), C101.2, C102.2, C103.2, C104.2, C105.2, C107.2, C201.2, C202.2, C203.1, C204.2, C206.2, C207.2, C208.2, C209.2, C210.2, C211.2, C212.2, C213.2, C215.2, C301.2, C302.2, C303.1, C304.2, C306.2, C307.2, C308.2, C309.2, C310.2, C311.2, C312.2, C313.2, C314.2, C315.2, C316.2, C317.2, C501.2, C502.2, C503.2, C504.2, C505.2, C701.2, C702.2, C801.2, C802.2, C901.2, D101.2 (A2), D102.1 (K), D201.2 (A), D203.2 (A2), D204.1 (K), D301.2 (A), D302.2 (A2), D303.1 (K), D305.1 (K), H1.1, H2.1, H3.1, H4.1, J1.2, J2.MP (MountPin), J3.MP (MountPin), J4.2, J4.MP (MountPin), J5.2, J5.4, J5.6, J6.1, J6.MP (MountPin), J7.6, J7.MP (MountPin), J9.2, J10.1, J11.3, J11.4, J12.3, J12.4, J13.1, J14.1, Q201.2 (S), Q601.2 (S), Q602.2 (S), Q603.2 (S), Q604.2 (S), R102.2, R204.2, R206.2, R208.2, R210.2, R215.2, R304.2, R306.2, R308.2, R505.2, R510.2, R515.2, R519.2, R602.2, R606.2, R610.2, R904.2, TP24.1, TP25.1, U101.1 (A1), U101.2 (A0), U101.7 (GND), U201.7 (GND), U201.9 (EP), U202.1 (A1), U202.7 (GND), U301.7 (GND), U301.9 (EP), U302.1 (GND), U501.3 (E), U502.3 (E), U503.3 (E), U801.4 (GND), U801.5 (A2), U801.6 (A1), U801.7 (A0), U802.1 (A0), U802.2 (A1), U802.3 (A2), U802.8 (GND)
GPS_5V: C901.1, F901.2, J7.1
GPS_RXD_C: J7.2, R905.2, R908.1, TP17.1
GPS_SCL: J7.4, R909.2
GPS_SDA: J7.5, R910.2
GPS_TXD_C: J7.3, R906.1, R907.2, TP18.1
I2C_SCL: J9.10, Q902.3 (D), R404.2, R802.2, R909.1, TP20.1, U101.5 (SCL), U202.5 (SCL), U801.2 (SCL), U802.14 (SCL)
I2C_SDA: J9.9, Q901.3 (D), R405.2, R801.2, R910.1, TP19.1, U101.4 (SDA), U202.4 (SDA), U801.1 (SDA), U802.15 (SDA)
INA1_N: C106.2, R106.2, U101.9 (IN-)
INA1_P: C106.1, R105.2, U101.10 (IN+)
INA2_N: C214.2, R213.2, U202.9 (IN-)
INA2_P: C214.1, R212.2, U202.10 (IN+)
INH_G: Q201.1 (G), R209.2, R210.1
LED3V3_A: D305.2 (A), R313.2
LED12_A: D102.2 (A), R107.2
LEDESP_A: D303.2 (A), R310.2
LEDL_A: J2.3, R603.2, R604.2
LEDL_G: Q601.1 (G), R601.2, R602.1
LEDL_K: J2.4, Q601.3 (D)
LEDPI_A: D204.2 (A), R216.2
LEDR_A: J3.3, R607.2, R608.2
LEDR_G: Q602.1 (G), R605.2, R606.1
LEDR_K: J3.4, Q602.3 (D)
PI_AUX_C: J6.4, J14.4, Q901.1 (G), Q902.1 (G), R903.1, R911.1, R912.1
PI_PGOOD: A1.28 (IO15), R214.2, R215.1
PI_RXD: J6.3, J14.3, R902.2, TP16.1
PI_SCL: J6.6, Q902.2 (S), R912.2
PI_SDA: J6.5, Q901.2 (S), R911.2
PI_TXD: J6.2, J14.2, R901.1, TP15.1
POD_BTN: C504.1, J4.1, R516.2, R517.1, TP23.1
POD_BUZN: D601.2 (A), J4.4, Q603.3 (D)
POD_BUZP: D601.1 (K), F601.2, J4.3
Q101_G: Q101.1 (G), R101.2, R102.1
RT_ESP: R306.1, U301.4 (RT/CLK)
RT_PI: R206.1, U201.4 (RT/CLK)
SPI_MOSI: A2.6 (MOSI), J10.6, R401.2
SPI_SCK: A2.5 (SCK), J10.5, R402.2
SW_ESP: C305.2, D301.1 (K), L301.1, U301.8 (PH)
SW_PI: C205.2, D201.1 (K), L201.1, U201.8 (PH)
VIN_FUSED: D101.1 (A1), F101.2, Q101.2 (D)
VIN_RAW: F101.1, J1.1

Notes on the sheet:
1xx 12 V INPUT, PROTECTION, 12 V MONITOR
2xx 5V_PI BUCK (Pi + display) AND PI POWER CONTROL
3xx 5V_ESP BUCK AND 3.3 V
4xx ESP32 DEVKIT
5xx INPUTS: BLINKERS, AUX, BUTTON, ACC SENSE
6xx OUTPUTS: DOOR LEDS, PIEZO, FAN
7xx CC1101 315 MHz RADIO
8xx I2C: TEMPERATURE, I/O EXPANDER
9xx PI LINK, GPS
TEST PADS, MOUNTING HOLES
POWER FLAGS (rails driven through passives)

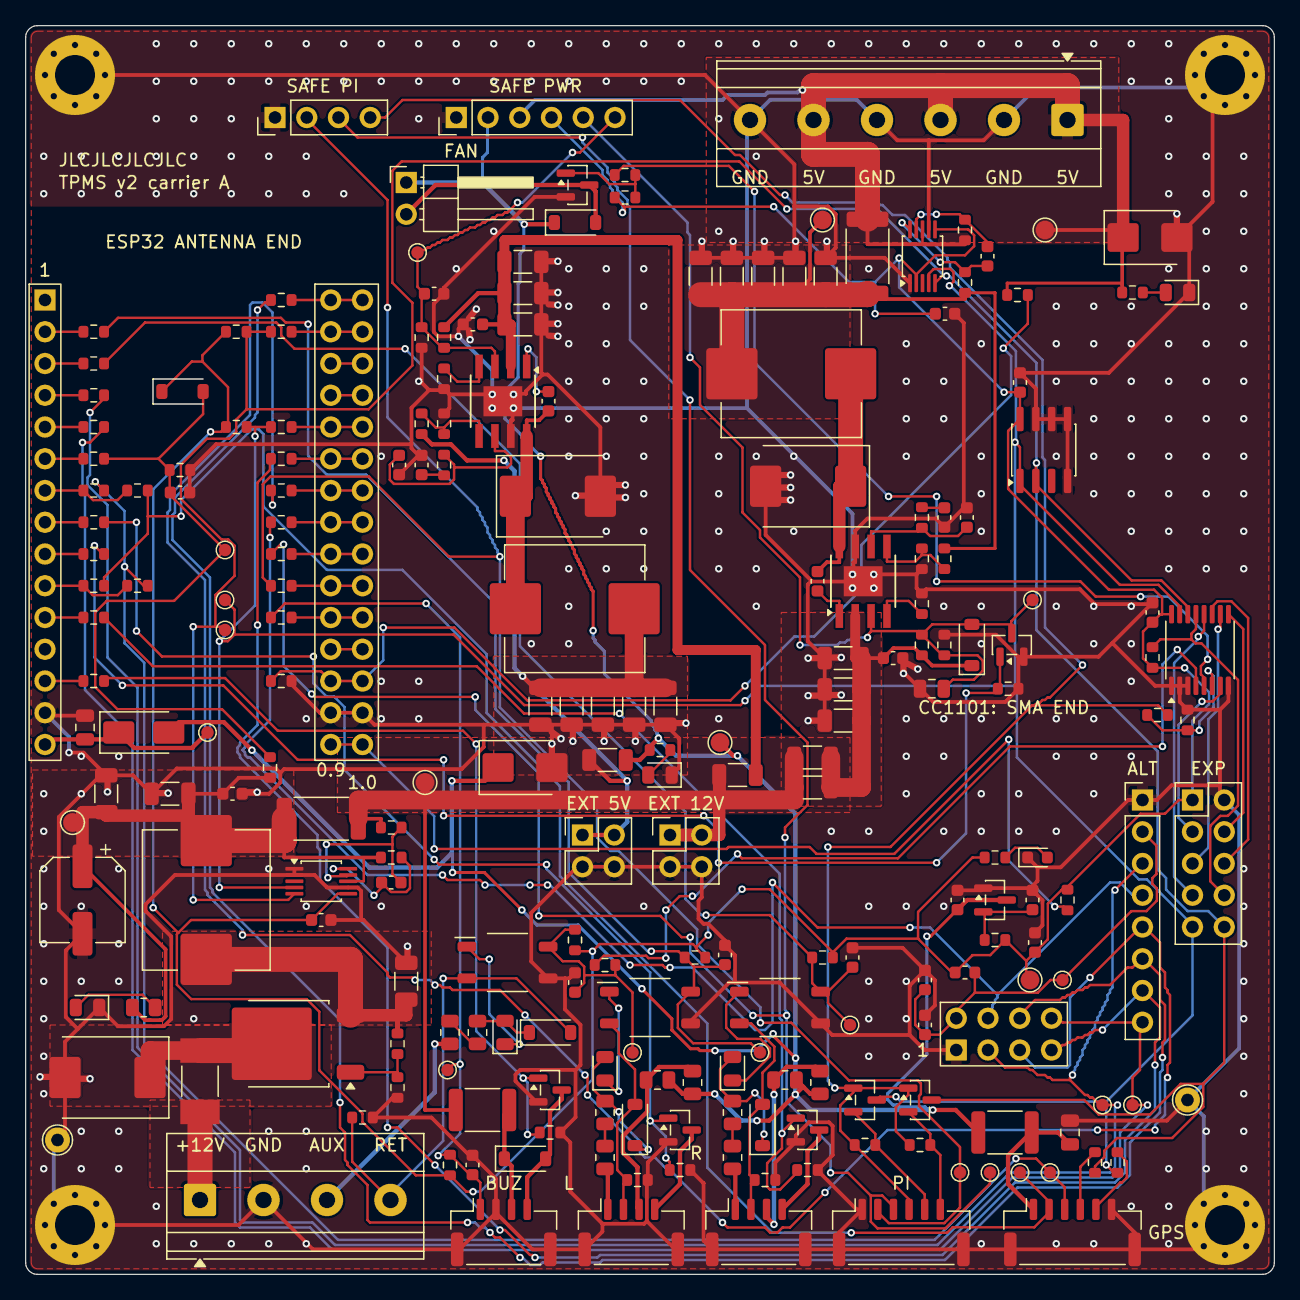
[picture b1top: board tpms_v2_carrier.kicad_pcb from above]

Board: 2 copper layers, 99.9 x 99.9 mm, 228 parts (0 on the bottom side), 120 nets.
